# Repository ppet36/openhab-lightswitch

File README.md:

# OpenHAB light switch

This repository encapsulates Cadsoft's Eagle files and firmware for OpenHAB light switch using ESP8266-01 module. There is single variant under switch with relay and single/double variants with relays/triacs for round wiring boxes.

For powering module can be used any 5V/ >=800mA power supply such as USB charger for phone. Power consumption with AKYGA CCABKEYAKY-07310 power supply is about 1.2W.

Schematics is very simple. For single variant GPIO0 of ESP8266 is used for driving relay/triac and GPIO2 for observation of original switch. Light can be turned on / off using original switch or OpenHAB admin screen. For double variant is used I/O expander PCA9536 which two pins used for driving relays/triacs and other two for switches observation.

For uploading code to ESP8266 is needed Arduino. In source code is needed to specify WIFI AP parameters, network parameters, OpenHAB item name as well as address where OpenHAB server listens. After module startup is on his IP address available HTTP server where some parameters can be redefined. It's useful in case for example changing WIFI password.

For handle lightswitch in OpenHAB you need to modify you sitemap, items and rules file. In items file (/configurations/items/&lt;yourname&gt;.items) is needed to define new item:
```
Switch bathroomMirror "Bathroom (mirror light)"
```
Now you can define rule in rules file (/configurations/rules/&lt;yourname&gt;.rules), which sends request to IP address of module whenever the status changes. Instead of 192.168.128.200 is need to specify IP address of your module.
```
rule bathroomMirror
when
  Item bathroomMirror changed
then 
  if (bathroomMirror.state == ON) {
    sendHttpGetRequest("http://192.168.128.200:80/ON")
  } else {
    sendHttpGetRequest("http://192.168.128.200:80/OFF")
  }
end 
```
Finally can be switch presented in sitemap file (/configurations/sitemaps/&lt;yourname&gt;.sitemap):
```
Switch item=bathroomMirror
```
It's easy and it looks pretty good:

##Schematics:
### Single relay

### Double relay

### Single triac

### Double triac

##PCBs:
PCB is realized as single-sided with some wire jumpers. ESP8266 is mounted as always in socket to enable firmware update. Depending of interferences you may need solder some 100n capacitors directly to ICs pads from bottom side of PCB.

###Some project images:

Module with power supply

Already mounted on its place

PCA9536 breadboard modules

Double relay version

Single triac version

Double triac version

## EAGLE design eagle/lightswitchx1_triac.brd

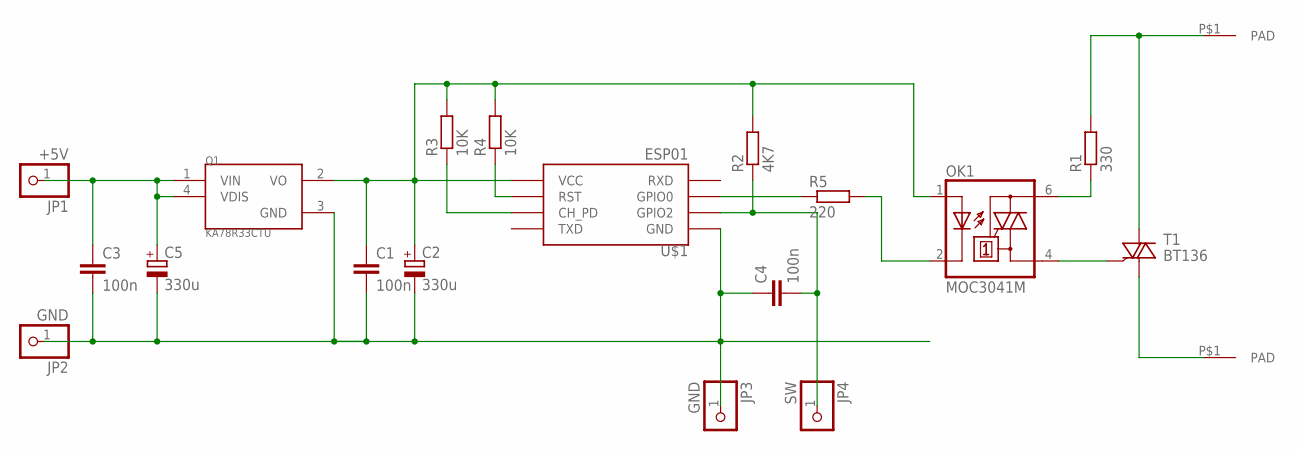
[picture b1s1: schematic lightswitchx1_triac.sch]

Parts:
C1, C3, C4: 100n; C025-030X050
C2, C5: 330u; E2-5
JP1: +5V; 1X01
JP2, JP3: GND; 1X01
JP4: SW; 1X01
OK1: MOC3041M; DIL06
Q1: KA78R33CTU; TO-220-4
R1: 330; 0207/7
R2: 4K7; 0207/10
R3, R4: 10K; 0207/10
R5: 220; 0207/7
T1: BT136; TO220AB
U$1: ESP01
U$4, U$5: PAD

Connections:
unnamed: C4.2, JP4.1, R2.1, U$1.GPIO2
unnamed: C1.2, C2.-, C3.2, C4.1, C5.-, JP2.1, JP3.1, Q1.3 (GND), U$1.GND
unnamed: C1.1, C2.+, OK1.1 (A), Q1.2 (VO), R2.2, R3.2, R4.2, U$1.VCC
unnamed: OK1.4 (A1), T1.3 (G)
unnamed: C3.1, C5.+, JP1.1, Q1.1 (VIN), Q1.4 (VDIS)
unnamed: R5.1, U$1.GPIO0
unnamed: OK1.6 (A2), R1.1
unnamed: R4.1, U$1.RST
unnamed: R3.1, U$1.CH_PD
unnamed: R1.2, T1.2 (A2), U$5.P$1
unnamed: T1.1 (A1), U$4.P$1
unnamed: OK1.2 (C), R5.2

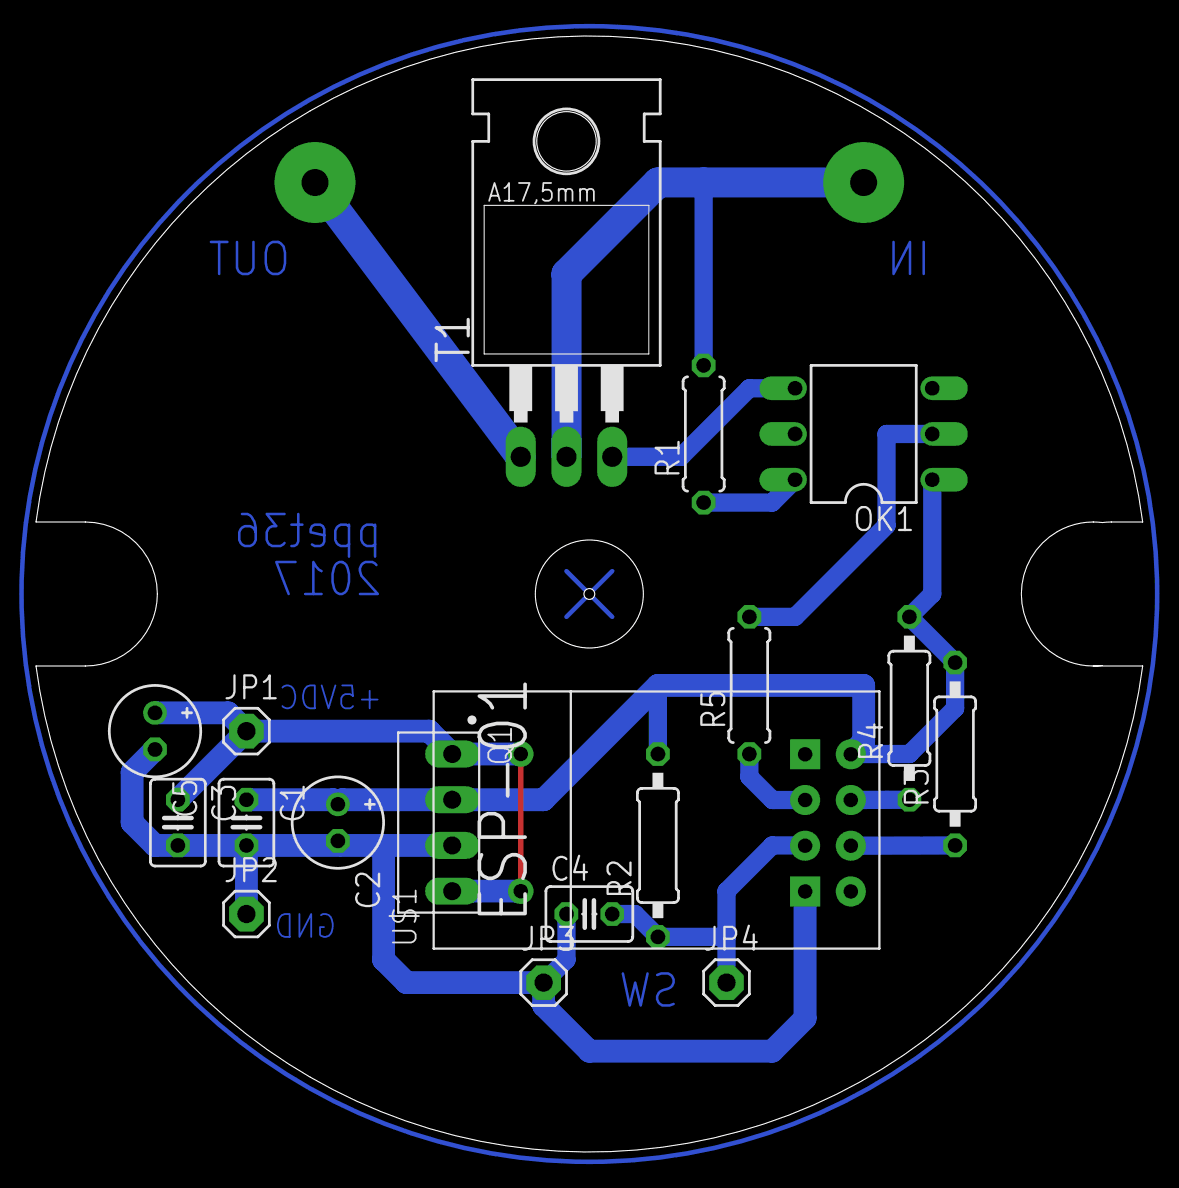
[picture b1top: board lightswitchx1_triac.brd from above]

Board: 2 copper layers, 61.5 x 62.0 mm, 20 parts (0 on the bottom side), 12 nets.

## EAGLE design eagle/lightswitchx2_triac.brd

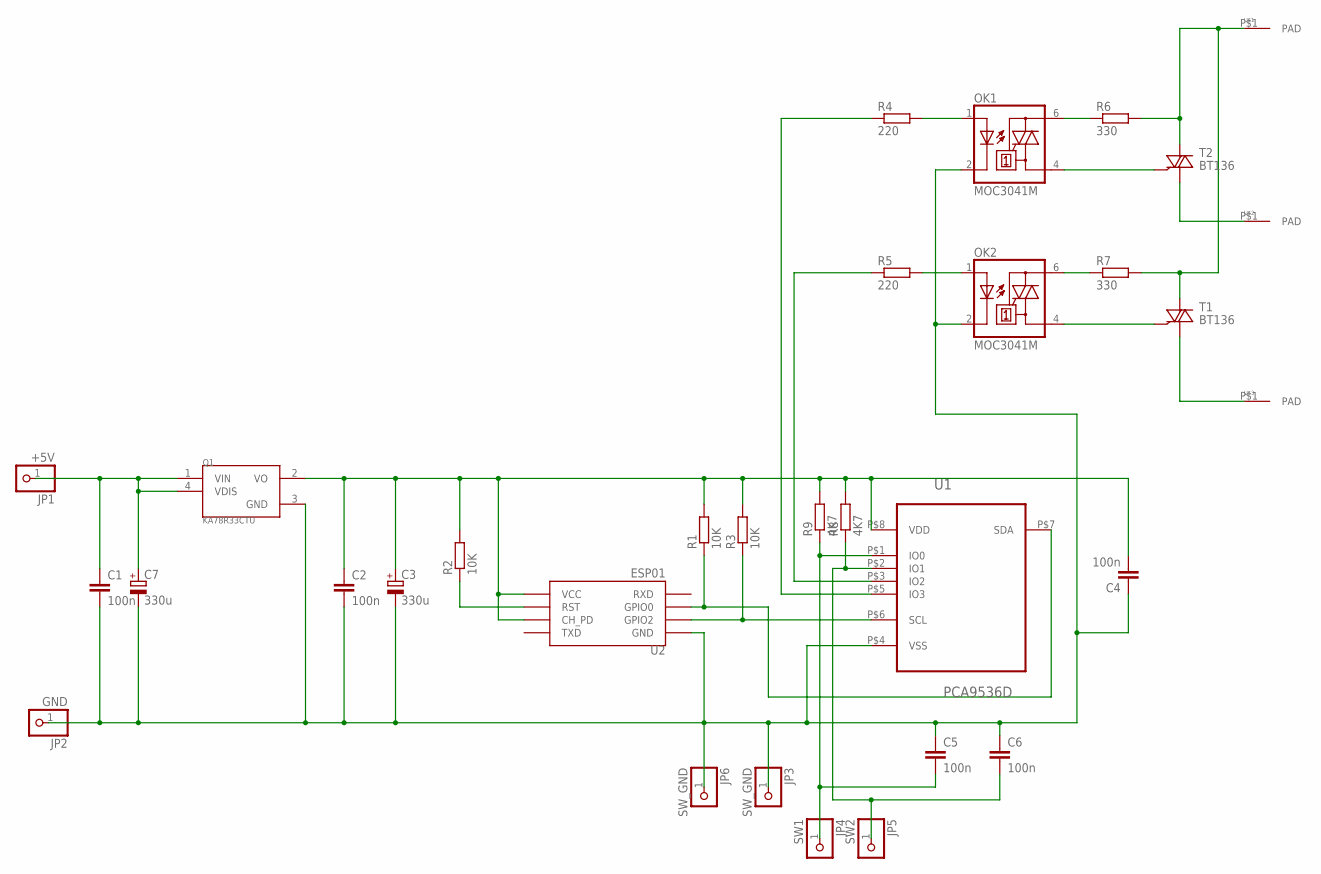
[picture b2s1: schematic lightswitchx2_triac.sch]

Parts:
C1, C2, C4, C5, C6: 100n; C050-024X044
C3, C7: 330u; E2-5
JP1: +5V; 1X01
JP2: GND; 1X01
JP3, JP6: SW_GND; 1X01-CLEANBIG
JP4: SW1; 1X01-CLEANBIG
JP5: SW2; 1X01-CLEANBIG
OK1, OK2: MOC3041M; DIL06
Q1: KA78R33CTU; TO-220-4
R1: 10K; 0207/10
R2, R3: 10K; 0204/7
R4, R5: 220; 0207/7
R6, R7: 330; 0207/7
R8: 4K7; 0207/7
R9: 4K7; 0207/10
T1, T2: BT136; TO220AB
U1: PCA9536D; ADAPTER
U2: ESP01
U$1, U$2, U$3: PAD

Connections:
unnamed: C1.1, C7.+, JP1.1, Q1.1 (VIN), Q1.4 (VDIS)
unnamed: R4.1, U1.P$5 (IO3)
unnamed: OK1.1 (A), R4.2
unnamed: R1.1, U1.P$7 (SDA), U2.GPIO0
unnamed: OK2.1 (A), R5.2
unnamed: R3.1, U1.P$6 (SCL), U2.GPIO2
unnamed: R2.1, U2.RST
unnamed: OK2.6 (A2), R7.1
unnamed: R5.1, U1.P$3 (IO2)
unnamed: OK1.6 (A2), R6.1
unnamed: C5.2, JP4.1, R9.1, U1.P$1 (IO0)
unnamed: R6.2, R7.2, T1.2 (A2), T2.2 (A2), U$1.P$1
unnamed: C6.2, JP5.1, R8.1, U1.P$2 (IO1)
unnamed: OK1.4 (A1), T2.3 (G)
unnamed: OK2.4 (A1), T1.3 (G)
unnamed: T2.1 (A1), U$2.P$1
unnamed: T1.1 (A1), U$3.P$1
VDD: C2.1, C3.+, C4.2, Q1.2 (VO), R1.2, R2.2, R3.2, R8.2, R9.2, U1.P$8 (VDD), U2.CH_PD, U2.VCC
VSS: C1.2, C2.2, C3.-, C4.1, C5.1, C6.1, C7.-, JP2.1, JP3.1, JP6.1, OK1.2 (C), OK2.2 (C), Q1.3 (GND), U1.P$4 (VSS), U2.GND

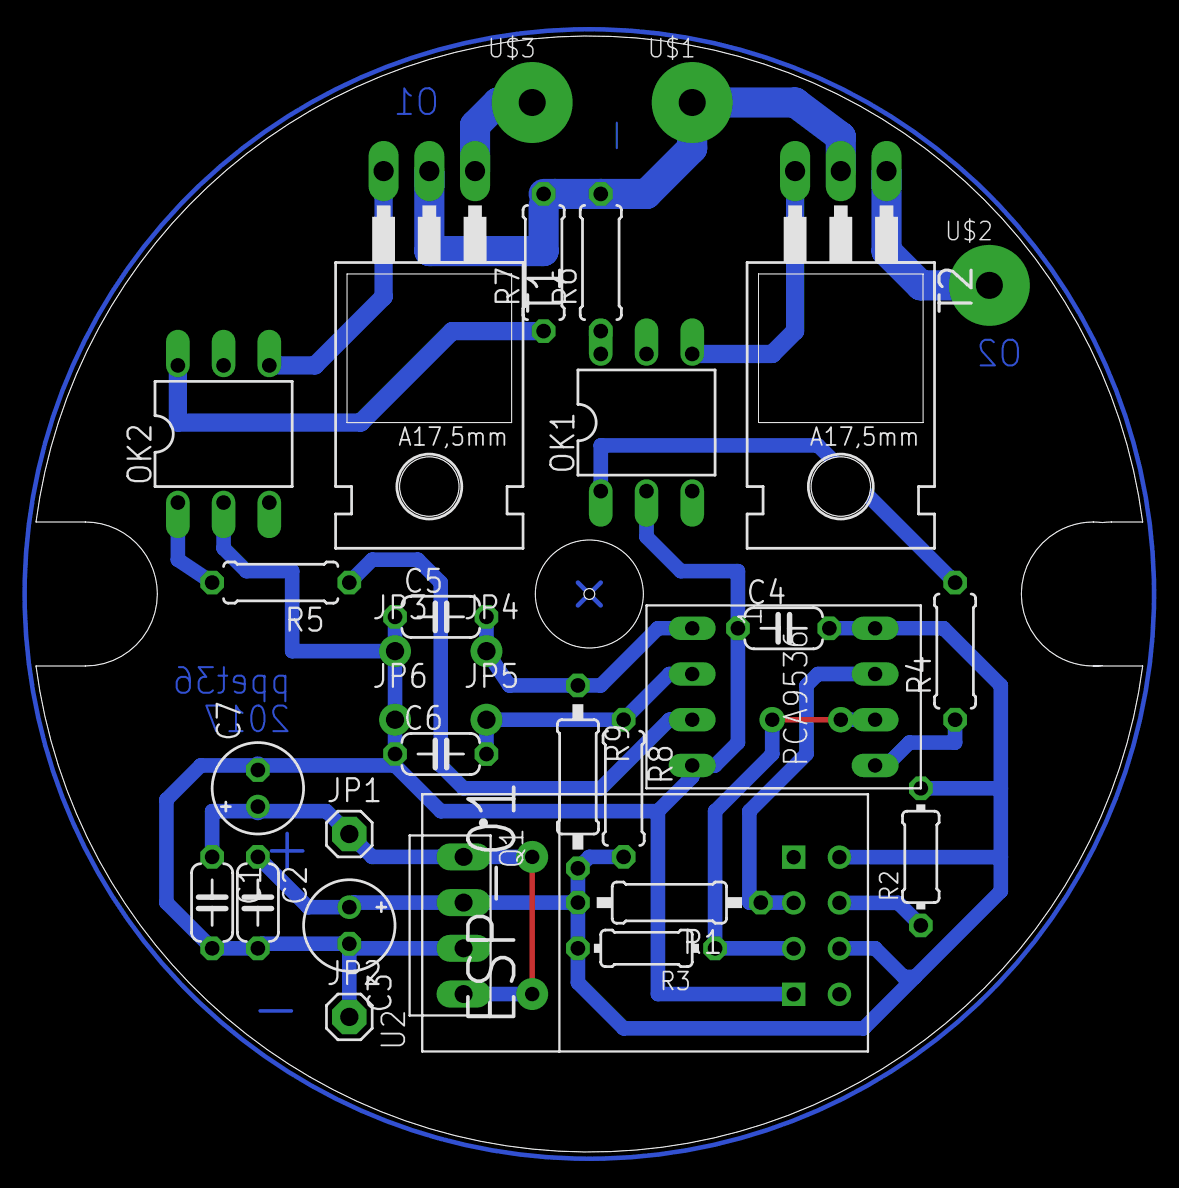
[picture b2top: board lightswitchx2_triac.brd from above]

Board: 2 copper layers, 61.5 x 62.0 mm, 32 parts (0 on the bottom side), 19 nets.

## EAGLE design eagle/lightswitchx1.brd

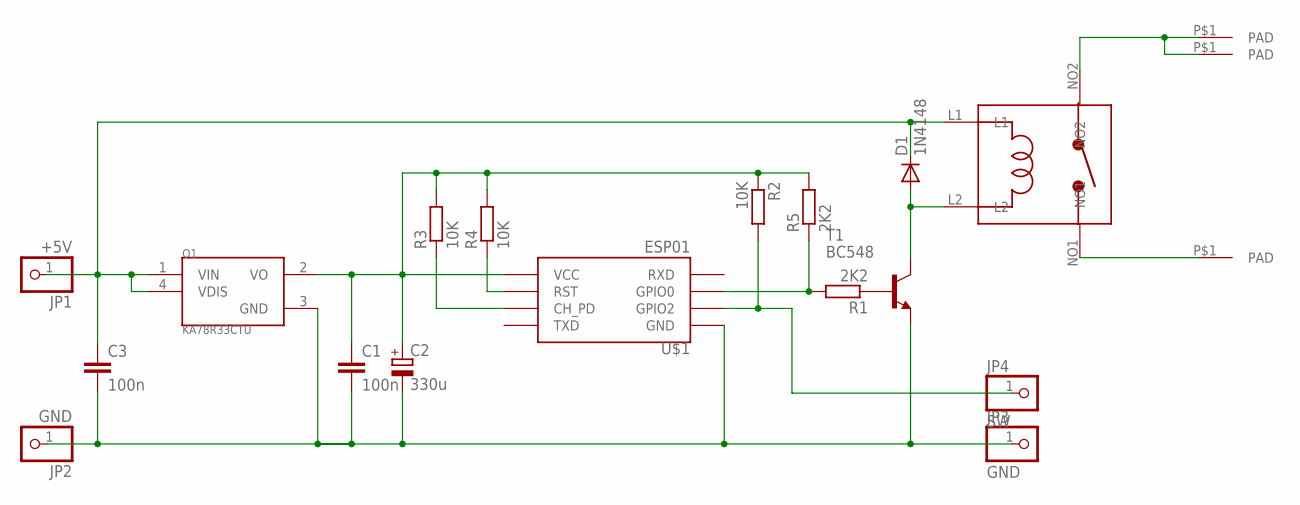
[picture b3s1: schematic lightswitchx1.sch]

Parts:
C1, C3: 100n; C025-030X050
C2: 330u; E2-5
D1: 1N4148; DO35-7
JP1: +5V; 1X01
JP2, JP3: GND; 1X01
JP4: SW; 1X01
Q1: KA78R33CTU; TO-220-4
R1, R5: 2K2; 0207/10
R2, R3, R4: 10K; 0207/10
T1: BC548; TO92
U$1: ESP01
U$2: LEG1A-5; LEG-1A-5
U$3, U$4, U$5: PAD

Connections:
unnamed: JP4.1, R2.2, U$1.GPIO2
unnamed: C1.2, C2.-, C3.2, JP2.1, JP3.1, Q1.3 (GND), T1.1 (E), U$1.GND
unnamed: C1.1, C2.+, Q1.2 (VO), R2.1, R3.2, R4.2, R5.2, U$1.VCC
unnamed: D1.A, T1.3 (C), U$2.L2
unnamed: C3.1, D1.C, JP1.1, Q1.1 (VIN), Q1.4 (VDIS), U$2.L1
unnamed: R1.2, R5.1, U$1.GPIO0
unnamed: R1.1, T1.2 (B)
unnamed: R4.1, U$1.RST
unnamed: R3.1, U$1.CH_PD
unnamed: U$2.NO2, U$3.P$1, U$5.P$1
unnamed: U$2.NO1, U$4.P$1

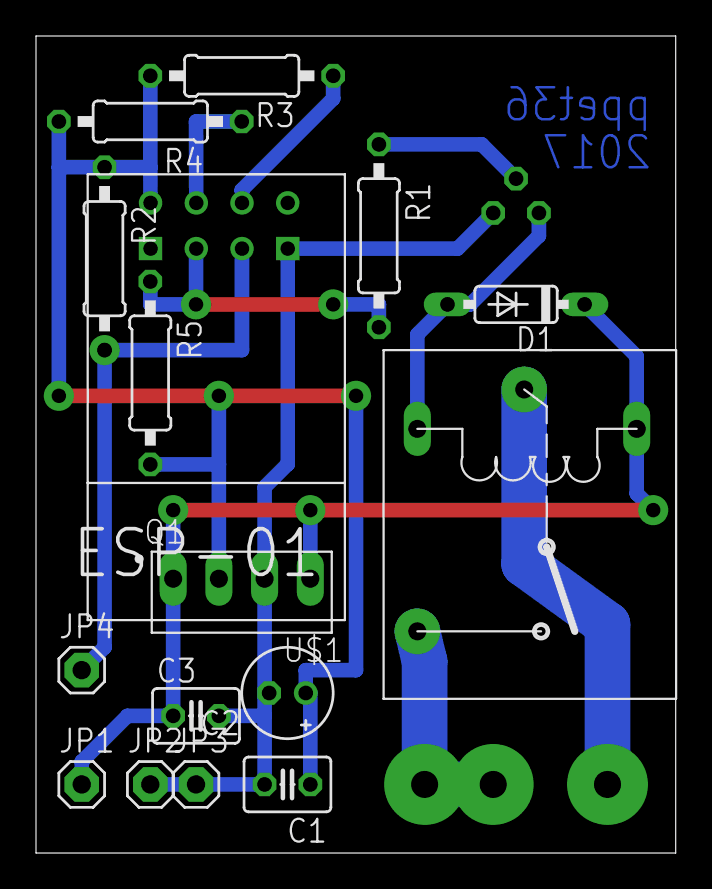
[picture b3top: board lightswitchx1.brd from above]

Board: 2 copper layers, 35.5 x 45.4 mm, 20 parts (1 on the bottom side), 11 nets.

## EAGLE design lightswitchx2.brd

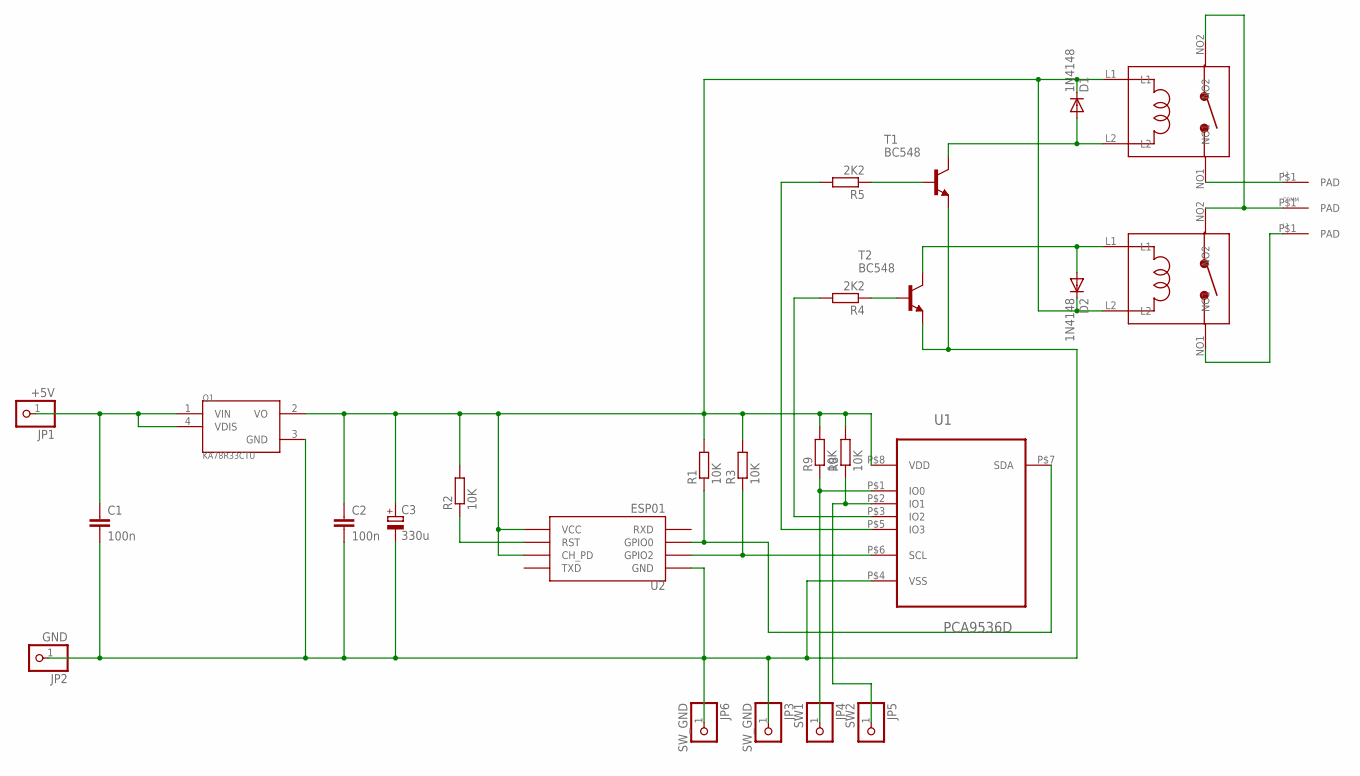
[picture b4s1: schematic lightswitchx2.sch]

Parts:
C1, C2: 100n; C050-024X044
C3: 330u; E2-5
COMM: PAD
D1, D2: 1N4148; DO35-7
JP1: +5V; 1X01
JP2: GND; 1X01
JP3, JP6: SW_GND; 1X01-CLEANBIG
JP4: SW1; 1X01-CLEANBIG
JP5: SW2; 1X01-CLEANBIG
L1: L1; PAD
L2: X; PAD
Q1: KA78R33CTU; TO-220-4
R1, R9: 10K; 0207/10
R2, R3: 10K; 0204/7
R4, R5: 2K2; 0204/7
R8: 10K; 0207/7
REL1, REL2: LEG1A-5; LEG-1A-5
T1, T2: BC548; TO92-EBC
U1: PCA9536D; ADAPTER
U2: ESP01

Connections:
unnamed: C1.1, JP1.1, Q1.1 (VIN), Q1.4 (VDIS)
unnamed: R5.2, U1.P$5 (IO3)
unnamed: L1.P$1, REL1.NO1
unnamed: R1.1, U1.P$7 (SDA), U2.GPIO0
unnamed: COMM.P$1, REL1.NO2, REL2.NO2
unnamed: R3.1, U1.P$6 (SCL), U2.GPIO2
unnamed: R2.1, U2.RST
unnamed: R5.1, T1.B
unnamed: R4.2, U1.P$3 (IO2)
unnamed: R4.1, T2.B
unnamed: JP4.1, R9.1, U1.P$1 (IO0)
unnamed: L2.P$1, REL2.NO1
unnamed: D1.A, REL2.L2, T1.C
unnamed: JP5.1, R8.1, U1.P$2 (IO1)
unnamed: D2.A, REL1.L1, T2.C
VDD: C2.1, C3.+, D1.C, D2.C, Q1.2 (VO), R1.2, R2.2, R3.2, R8.2, R9.2, REL1.L2, REL2.L1, U1.P$8 (VDD), U2.CH_PD, U2.VCC
VSS: C1.2, C2.2, C3.-, JP2.1, JP3.1, JP6.1, Q1.3 (GND), T1.E, T2.E, U1.P$4 (VSS), U2.GND

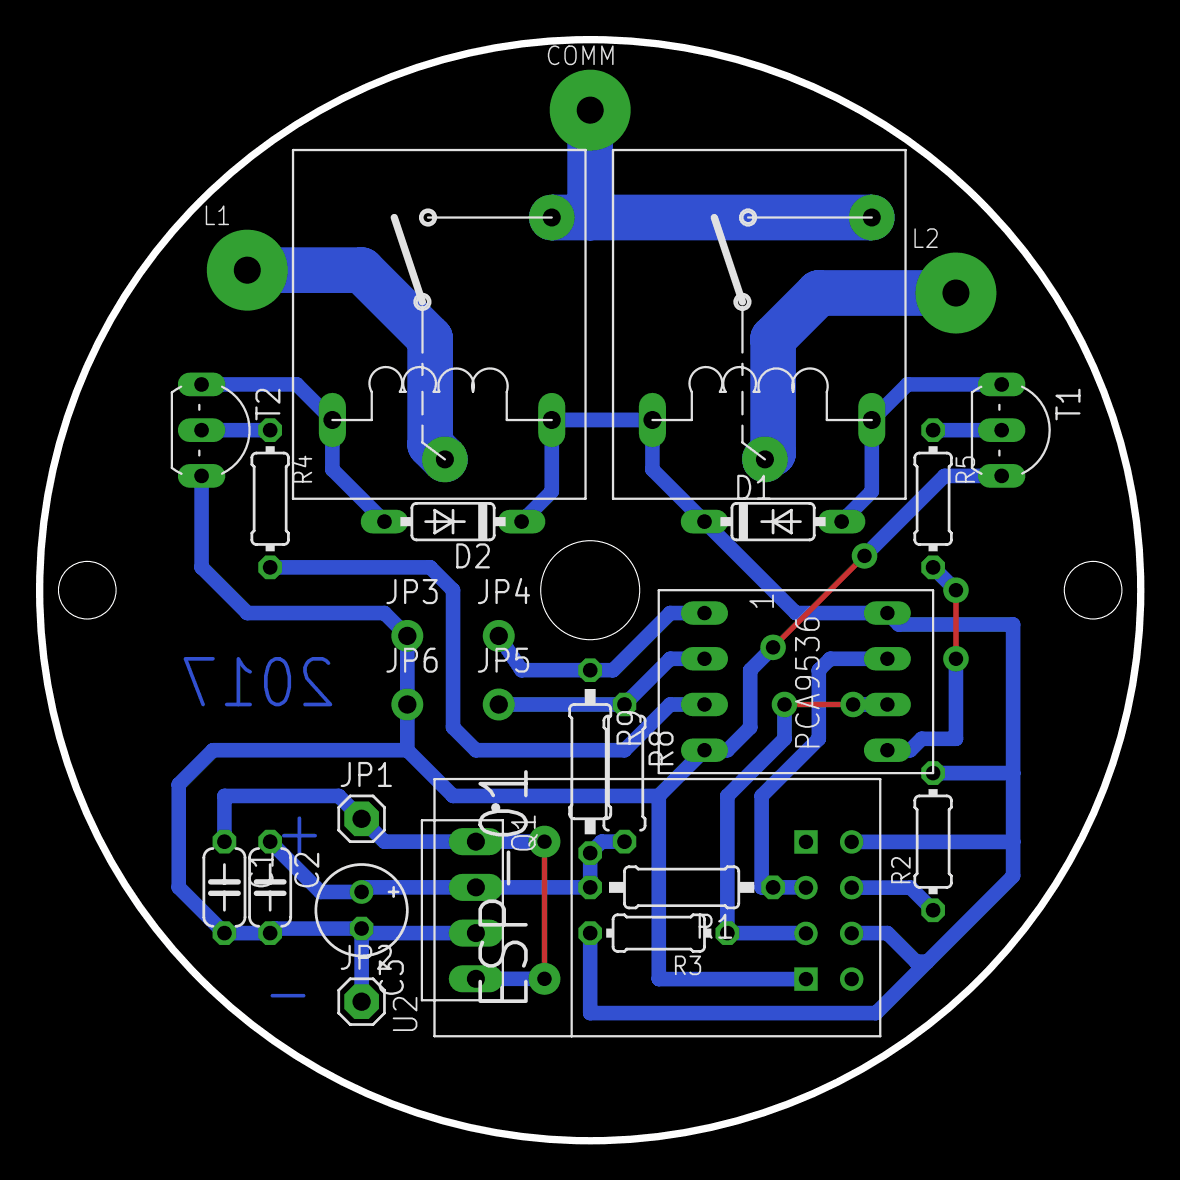
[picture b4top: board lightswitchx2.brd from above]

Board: 2 copper layers, 61.2 x 61.2 mm, 28 parts (0 on the bottom side), 17 nets.

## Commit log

2017-01-12 Added some 100n capacitors
2017-01-13 Modified switch read routine for eliminate interference
2017-01-13 Added some capacitors to eliminate interference
2017-01-16 Added measured power consumption
